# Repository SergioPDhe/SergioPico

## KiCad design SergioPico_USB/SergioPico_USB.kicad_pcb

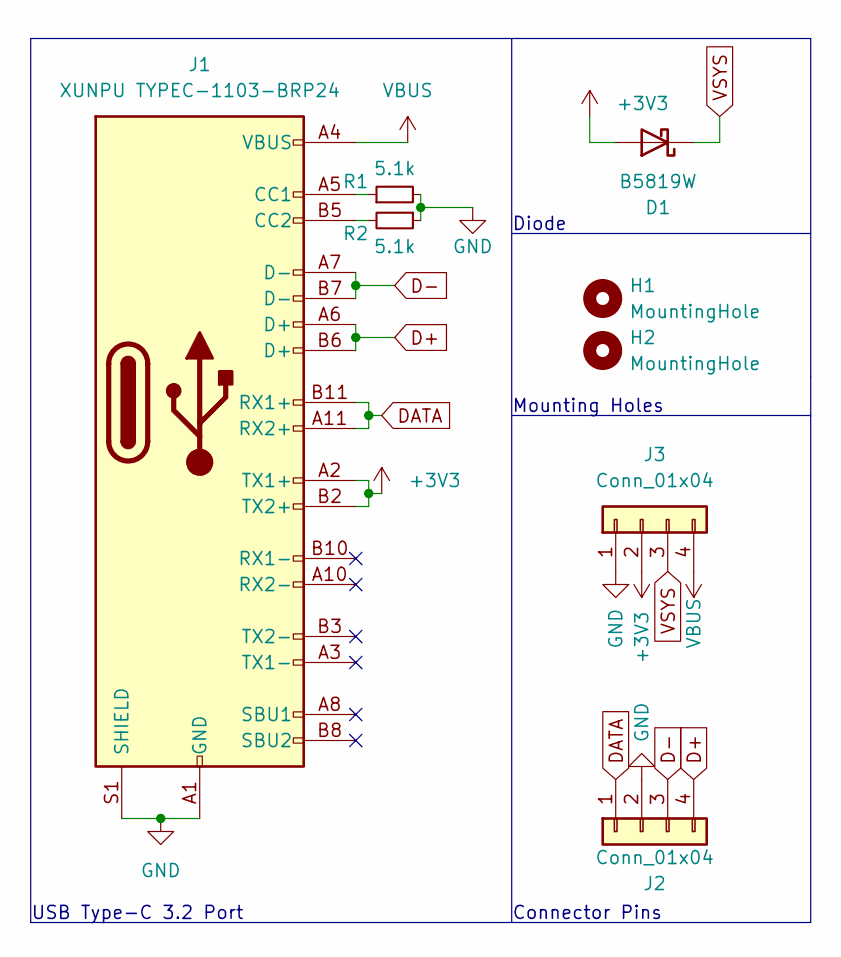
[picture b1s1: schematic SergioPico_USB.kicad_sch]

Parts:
D1: B5819W; D_SOD-123
H1, H2: MountingHole; MountingHole_4.3mm_M4
J1: XUNPU TYPEC-1103-BRP24; Xunpu C2856665 USBC Straddle Mount
J2, J3: Conn_01x04; PinSocket_1x04_P2.54mm_Vertical
R1, R2: 5.1k; R_0603_1608Metric

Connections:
+3V3: D1.2 (A), J1.A2 (TX1+), J1.B2 (TX2+), J3.2
D+: J1.A6 (D+), J1.B6 (D+), J2.4
D-: J1.A7 (D-), J1.B7 (D-), J2.3
DATA: J1.A11 (RX2+), J1.B11 (RX1+), J2.1
GND: J1.A1 (GND), J1.A12 (GND), J1.B1 (GND), J1.B12 (GND), J1.S1 (SHIELD), J2.2, J3.1, R1.2, R2.1
unnamed: J1.A5 (CC1), R1.1
unnamed: J1.B5 (CC2), R2.2
VBUS: J1.A4 (VBUS), J1.A9 (VBUS), J1.B4 (VBUS), J1.B9 (VBUS), J3.4
VSYS: D1.1 (K), J3.3

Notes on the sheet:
USB Type-C 3.2 Port
Mounting Holes
Connector Pins
Diode

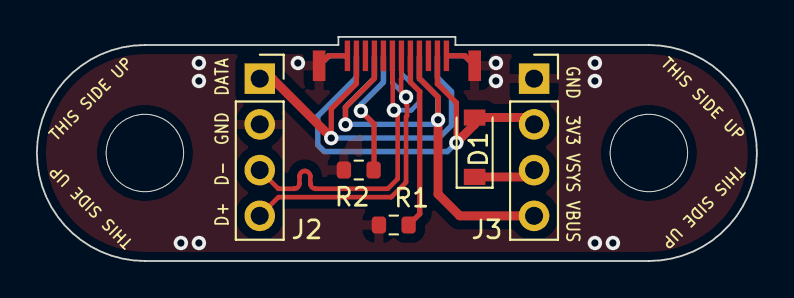
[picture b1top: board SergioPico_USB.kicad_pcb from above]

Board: 2 copper layers, 40.0 x 12.5 mm, 8 parts (0 on the bottom side), 9 nets.

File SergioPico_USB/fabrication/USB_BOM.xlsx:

Comment | Designator | Footprint | JLBPCB part #
B5819W | D1 | Diode_SMD:D_SOD-123 | C8598
XUNPU TYPEC-1103-BRP24 | J1 | Sergio_footprints:Xunpu C2856665 USBC Straddle Mount | C2856665
5.1k | R1, R2 | Resistor_SMD:R_0603_1608Metric | C23186

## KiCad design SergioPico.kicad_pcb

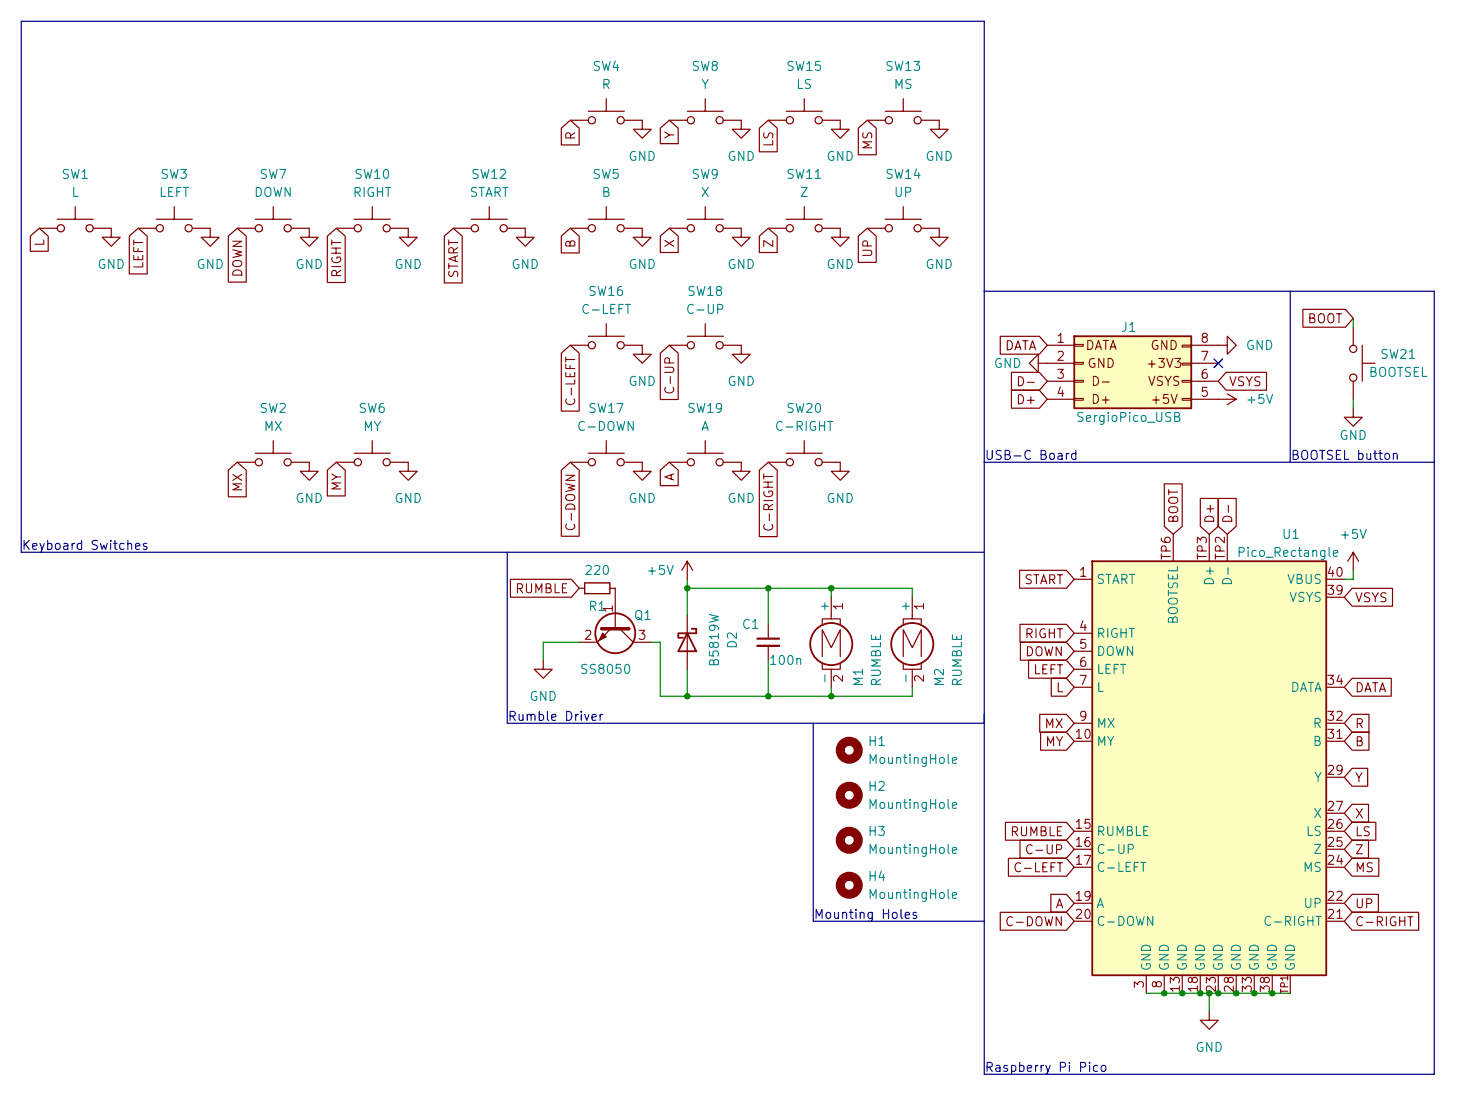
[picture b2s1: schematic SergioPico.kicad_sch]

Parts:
C1: 100n; C_0402_1005Metric_Pad0.74x0.62mm_HandSolder
D2: B5819W; D_SOD-123
H1, H2, H3, H4: MountingHole; MountingHole_4.3mm_M4
J1: SergioPico_USB
M1, M2: RUMBLE; PinHeader_1x02_P2.54mm_Vertical
Q1: SS8050; SOT-23_Handsoldering
R1: 220; R_0603_1608Metric_Pad0.98x0.95mm_HandSolder
SW1: L; SW_MX_1.00u_PCB_Hybrid
SW2: MX; SW_MX_1.00u_PCB_Hybrid
SW3: LEFT; SW_MX_1.00u_PCB_Hybrid
SW4: R; SW_MX_1.00u_PCB_Hybrid
SW5: B; SW_MX_1.00u_PCB_Hybrid
SW6: MY; SW_MX_1.00u_PCB_Hybrid
SW7: DOWN; SW_MX_1.00u_PCB_Hybrid
SW8: Y; SW_MX_1.00u_PCB_Hybrid
SW9: X; SW_MX_1.00u_PCB_Hybrid
SW10: RIGHT; SW_MX_1.00u_PCB_Hybrid
SW11: Z; SW_MX_1.00u_PCB_Hybrid
SW12: START; SW_MX_1.00u_PCB_Hybrid
SW13: MS; SW_MX_1.00u_PCB_Hybrid
SW14: UP; SW_MX_1.00u_PCB_Hybrid
SW15: LS; SW_MX_1.00u_PCB_Hybrid
SW16: C-LEFT; SW_MX_1.00u_PCB_Hybrid
SW17: C-DOWN; SW_MX_1.00u_PCB_Hybrid
SW18: C-UP; SW_MX_1.00u_PCB_Hybrid
SW19: A; SW_MX_1.00u_PCB_Hybrid
SW20: C-RIGHT; SW_MX_1.00u_PCB_Hybrid
SW21: BOOTSEL; PinHeader_1x02_P2.54mm_Vertical
U1: Pico_Rectangle; RPi_Pico_Removed3Pins

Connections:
+5V: C1.1, D2.1 (K), J1.5, M1.1 (+), M2.1 (+), U1.40 (VBUS)
A: SW19.1, U1.19 (A)
B: SW5.1, U1.31 (B)
BOOT: SW21.1, U1.TP6 (BOOTSEL)
C-DOWN: SW17.1, U1.20 (C-DOWN)
C-LEFT: SW16.1, U1.17 (C-LEFT)
C-RIGHT: SW20.1, U1.21 (C-RIGHT)
C-UP: SW18.1, U1.16 (C-UP)
D+: J1.4, U1.TP3 (D+)
D-: J1.3, U1.TP2 (D-)
DATA: J1.1, U1.34 (DATA)
DOWN: SW7.1, U1.5 (DOWN)
GND: J1.2, J1.8, Q1.2 (E), SW1.2, SW2.2, SW3.2, SW4.2, SW5.2, SW6.2, SW7.2, SW8.2, SW9.2, SW10.2, SW11.2, SW12.2, SW13.2, SW14.2, SW15.2, SW16.2, SW17.2, SW18.2, SW19.2, SW20.2, SW21.2, U1.3 (GND), U1.8 (GND), U1.13 (GND), U1.18 (GND), U1.23 (GND), U1.28 (GND), U1.33 (GND), U1.38 (GND), U1.TP1 (GND)
L: SW1.1, U1.7 (L)
LEFT: SW3.1, U1.6 (LEFT)
LS: SW15.1, U1.26 (LS)
MS: SW13.1, U1.24 (MS)
MX: SW2.1, U1.9 (MX)
MY: SW6.1, U1.10 (MY)
unnamed: C1.2, D2.2 (A), M1.2 (-), M2.2 (-), Q1.3 (C)
unnamed: Q1.1 (B), R1.2
R: SW4.1, U1.32 (R)
RIGHT: SW10.1, U1.4 (RIGHT)
RUMBLE: R1.1, U1.15 (RUMBLE)
START: SW12.1, U1.1 (START)
UP: SW14.1, U1.22 (UP)
VSYS: J1.6, U1.39 (VSYS)
X: SW9.1, U1.27 (X)
Y: SW8.1, U1.29 (Y)
Z: SW11.1, U1.25 (Z)

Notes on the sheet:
USB-C Board
BOOTSEL button
Raspberry Pi Pico
Rumble Driver
Mounting Holes
Keyboard Switches

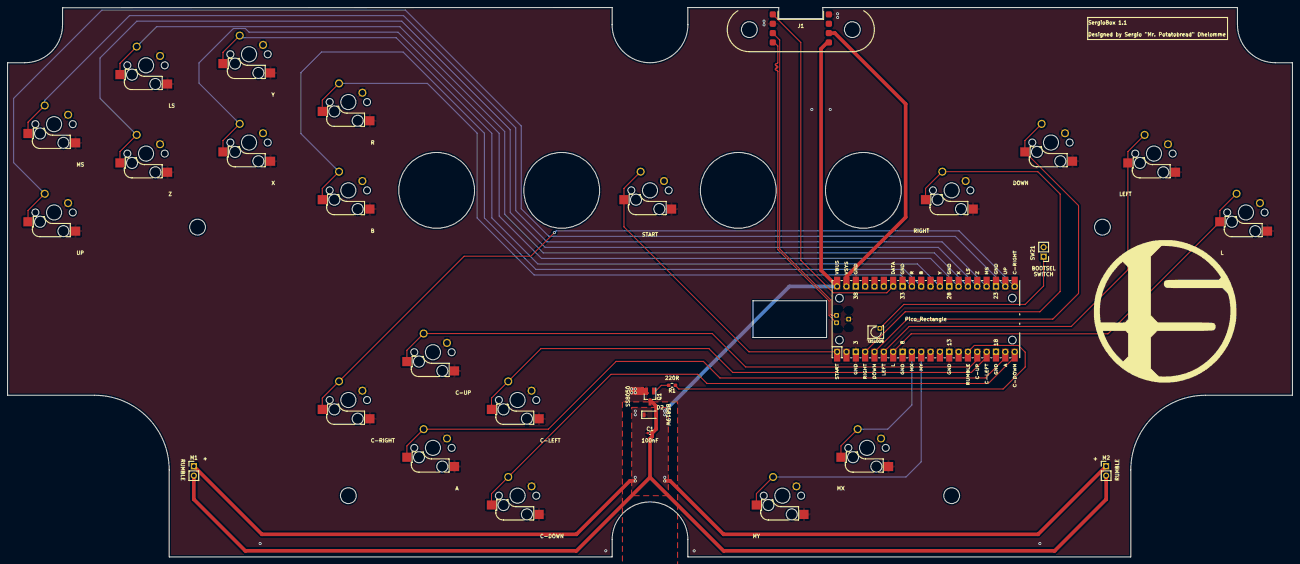
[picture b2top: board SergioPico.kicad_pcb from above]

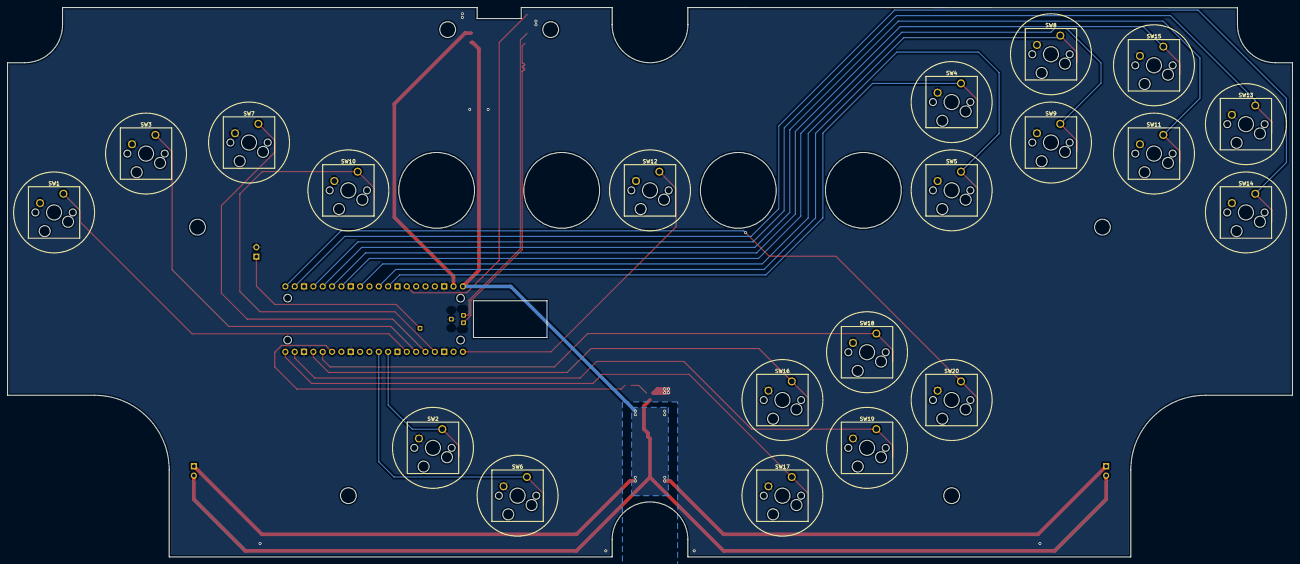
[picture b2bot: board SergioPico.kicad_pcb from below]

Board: 2 copper layers, 349.3 x 149.4 mm, 33 parts (20 on the bottom side), 30 nets.

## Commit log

2023-11-24 commit of all work done
2023-11-24 added models
